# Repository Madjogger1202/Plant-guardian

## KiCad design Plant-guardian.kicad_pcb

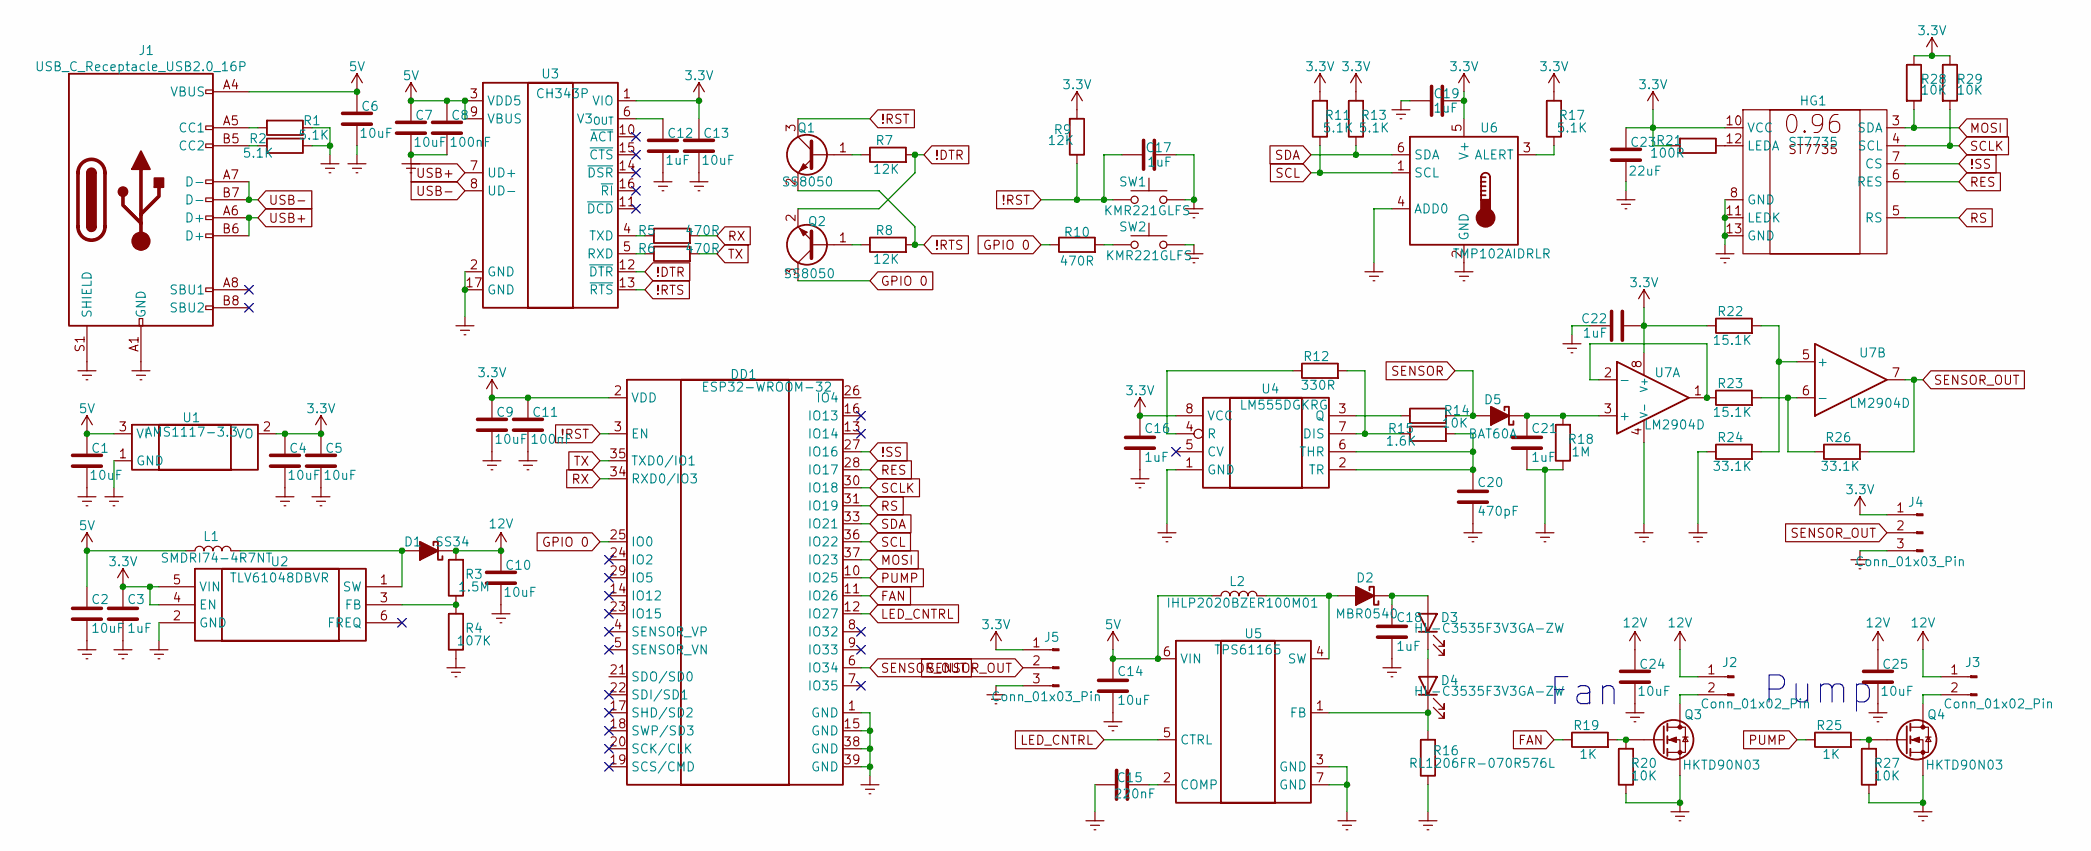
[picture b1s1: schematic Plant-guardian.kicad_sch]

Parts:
C1, C2, C4, C5, C6, C7, C9, C10, C13, C14, C24, C25: 10uF; C_0402_1005Metric
C3, C12, C16, C17, C18, C19, C21, C22: 1uF; C_0402_1005Metric
C8, C11: 100nF; C_0402_1005Metric
C15: 220nF; C_0402_1005Metric
C20: 470pF; C_0402_1005Metric
C23: 22uF; C_0402_1005Metric
D1: SS34; D_SMC
D2: MBR0540; D_SOD-123
D3, D4: HL-C3535F3V3GA-ZW; SMD3535-3P
D5: BAT60A; D_SOD-323
DD1: ESP32-WROOM-32
HG1: ST7735; ST7735 0.96
J1: USB_C_Receptacle_USB2.0_16P; USB_C_Receptacle_GCT_USB4105-xx-A_16P_TopMnt_Horizontal
J2, J3: Conn_01x02_Pin; PinHeader_1x02_P2.54mm_Vertical
J4, J5: Conn_01x03_Pin; PinHeader_1x03_P2.54mm_Vertical
L1: SMDRI74-4R7NT; L_SXN_SMDRI73
L2: IHLP2020BZER100M01; L_APV_APH0518
Q1, Q2: SS8050; SOT-23
Q3, Q4: HKTD90N03; TO-252-2
R1, R2, R11, R13, R17: 5.1K; R_0402_1005Metric
R3: 1.5M; R_0402_1005Metric
R4: 107K; R_0402_1005Metric
R5, R6, R10: 470R; R_0402_1005Metric
R7, R8, R9: 12K; R_0402_1005Metric
R12: 330R; R_0402_1005Metric
R14, R20, R27, R28, R29: 10K; R_0402_1005Metric
R15: 1.6K; R_0402_1005Metric
R16: RL1206FR-070R576L; R_1206_3216Metric
R18: 1M; R_0402_1005Metric
R19, R25: 1K; R_0402_1005Metric
R21: 100R; R_0402_1005Metric
R22, R23: 15.1K; R_0402_1005Metric
R24, R26: 33.1K; R_0402_1005Metric
SW1, SW2: KMR221GLFS; SW_SPST_PTS810
U1: AMS1117-3.3; SOT-89-3
U2: TLV61048DBVR; SOT-23-6; Manufacturer_Part_Number TLV61048DBVR; Mouser Part Number 595-TLV61048DBVR
U3: CH343P; WCH_QFN-16-1EP_3x3mm_P0.5mm_EP1.8x1.8mm
U4: LM555DGKRG; VSSOP-8_3x3mm_P0.65mm
U5: TPS61165; WSON-6-1EP_2x2mm_P0.65mm_EP1x1.6mm
U6: TMP102AIDRLR; SOT-563
U7: LM2904D; SOIC-8_5.3x6.2mm_P1.27mm

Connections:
3.3V: C3.2, C4.1, C5.1, C9.1, C11.1, C13.1, C16.2, C19.2, C22.2, C23.1, DD1.2 (VDD), HG1.10 (VCC), J4.1, J5.1, R9.2, R11.2, R13.2, R17.2, R21.2, R22.1, R28.1, R29.1, U1.2 (VO), U2.4 (EN), U2.5 (VIN), U3.1 (VIO), U4.8 (VCC), U6.5 (V+), U7.8 (V+)
5V: C1.1, C2.2, C6.1, C7.1, C8.1, C14.2, J1.A4 (VBUS), J1.A9 (VBUS), J1.B4 (VBUS), J1.B9 (VBUS), L1.1, L2.1, U1.3 (VI), U3.3 (VDD5), U3.9 (VBUS), U5.6 (VIN)
12V: C10.1, C24.1, C25.1, D1.1 (K), J2.1, J3.1, R3.2
!DTR: Q2.2 (E), R7.2, U3.12 (~DTR)
!RST: C17.1, DD1.3 (EN), Q1.3 (C), R9.1, SW1.2
!RTS: Q1.2 (E), R8.2, U3.13 (~RTS)
!SS: DD1.27 (IO16), HG1.7 (CS)
Earth: C1.2, C2.1, C3.1, C4.2, C5.2, C6.2, C7.2, C8.2, C9.2, C10.2, C11.2, C12.2, C13.2, C14.1, C15.1, C16.1, C17.2, C18.1, C19.1, C20.1, C21.1, C22.1, C23.2, C24.2, C25.2, DD1.1 (GND), DD1.15 (GND), DD1.38 (GND), DD1.39 (GND), HG1.8 (GND), HG1.11 (LEDK), HG1.13 (GND), J1.A1 (GND), J1.A12 (GND), J1.B1 (GND), J1.B12 (GND), J1.S1 (SHIELD), J4.3, J5.3, Q3.3 (S), Q4.3 (S), R1.1, R2.2, R4.1, R16.1, R18.1, R20.1, R24.1, R27.1, SW1.1, SW2.1, U1.1 (GND), U2.2 (GND), U3.2 (GND), U3.17 (GND), U4.1 (GND), U5.3 (GND), U5.7 (GND), U6.2 (GND), U6.4 (ADD0), U7.4 (V-)
FAN: DD1.11 (IO26), R19.1
GPIO 0: DD1.25 (IO0), Q2.3 (C), R10.1
LED_CNTRL: DD1.12 (IO27), U5.5 (CTRL)
MOSI: DD1.37 (IO23), HG1.3 (SDA), R28.2
unnamed: D1.2 (A), L1.2, U2.1 (SW)
unnamed: D2.2 (A), L2.2, U5.4 (SW)
unnamed: C18.2, D2.1 (K), D3.2 (A)
unnamed: D3.1 (K), D4.2 (A)
unnamed: D4.1 (K), R16.2, U5.1 (FB)
unnamed: C21.2, D5.1 (K), R18.2, U7.3 (+)
unnamed: HG1.12 (LEDA), R21.1
unnamed: J1.A5 (CC1), R1.2
unnamed: J1.B5 (CC2), R2.1
unnamed: J2.2, Q3.2 (D)
unnamed: J3.2, Q4.2 (D)
unnamed: Q1.1 (B), R7.1
unnamed: Q2.1 (B), R8.1
unnamed: Q3.1 (G), R19.2, R20.2
unnamed: Q4.1 (G), R25.2, R27.2
unnamed: R10.2, SW2.2
unnamed: R3.1, R4.2, U2.3 (FB)
unnamed: R6.1, U3.5 (RXD)
unnamed: R5.1, U3.4 (TXD)
unnamed: C12.1, U3.6 (V3_{OUT})
unnamed: R12.2, R15.1, U4.7 (DIS)
unnamed: R14.1, U4.3 (Q)
unnamed: R12.1, U4.4 (R)
unnamed: C20.2, R15.2, U4.2 (TR), U4.6 (THR)
unnamed: C15.2, U5.2 (COMP)
unnamed: R17.1, U6.3 (ALERT)
unnamed: R23.1, U7.1, U7.2 (-)
unnamed: R22.2, R24.2, U7.5 (+)
unnamed: R23.2, R26.1, U7.6 (-)
PUMP: DD1.10 (IO25), R25.1
RES: DD1.28 (IO17), HG1.6 (RES)
RS: DD1.31 (IO19), HG1.5 (RS)
RX: DD1.34 (RXD0/IO3), R5.2
SCL: DD1.36 (IO22), R11.1, U6.1 (SCL)
SCLK: DD1.30 (IO18), HG1.4 (SCL), R29.2
SDA: DD1.33 (IO21), R13.1, U6.6 (SDA)
SENSOR: D5.2 (A), R14.2
SENSOR_OUT: DD1.6 (IO34), J4.2, J5.2, R26.2, U7.7
TX: DD1.35 (TXD0/IO1), R6.2
USB+: J1.A6 (D+), J1.B6 (D+), U3.7 (UD+)
USB-: J1.A7 (D-), J1.B7 (D-), U3.8 (UD-)

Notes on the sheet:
Pump
Fan

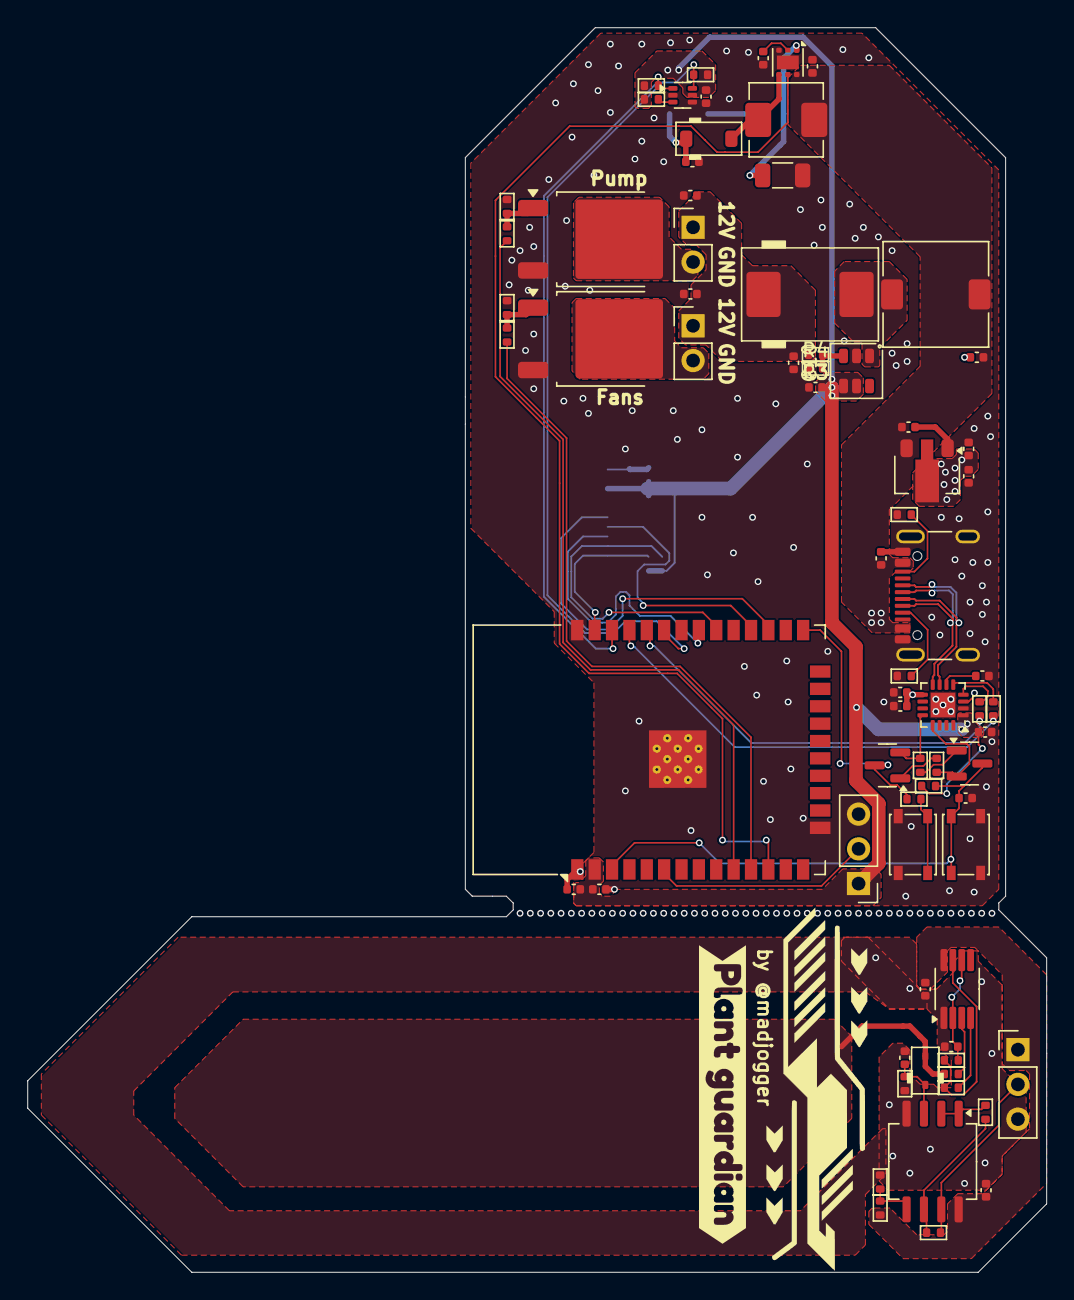
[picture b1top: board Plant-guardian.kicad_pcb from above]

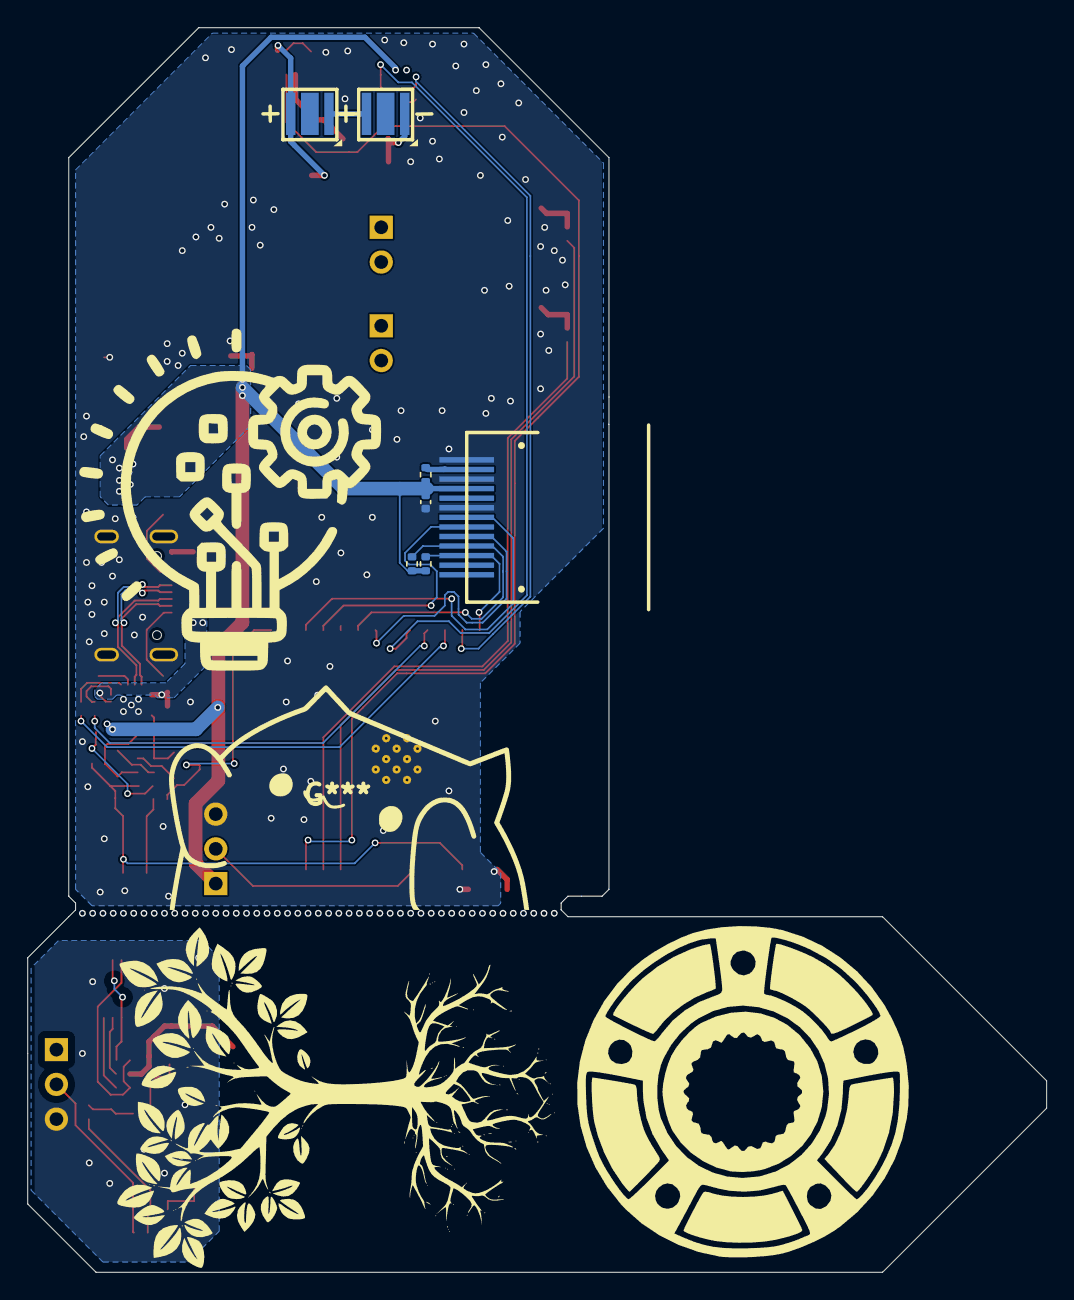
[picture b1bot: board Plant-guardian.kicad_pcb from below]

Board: 2 copper layers, 74.5 x 91.0 mm, 82 parts (7 on the bottom side), 53 nets.

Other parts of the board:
kibuzzard-691EE203: G***; kibuzzard-691EE203

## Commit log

2025-11-06 upd sch
2025-11-19 schematics done, placement on PCB done
2025-11-20 rev0 ready
